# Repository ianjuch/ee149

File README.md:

ee149 smart light switch project
=====
Gabe Buckmaster
Ian Juch

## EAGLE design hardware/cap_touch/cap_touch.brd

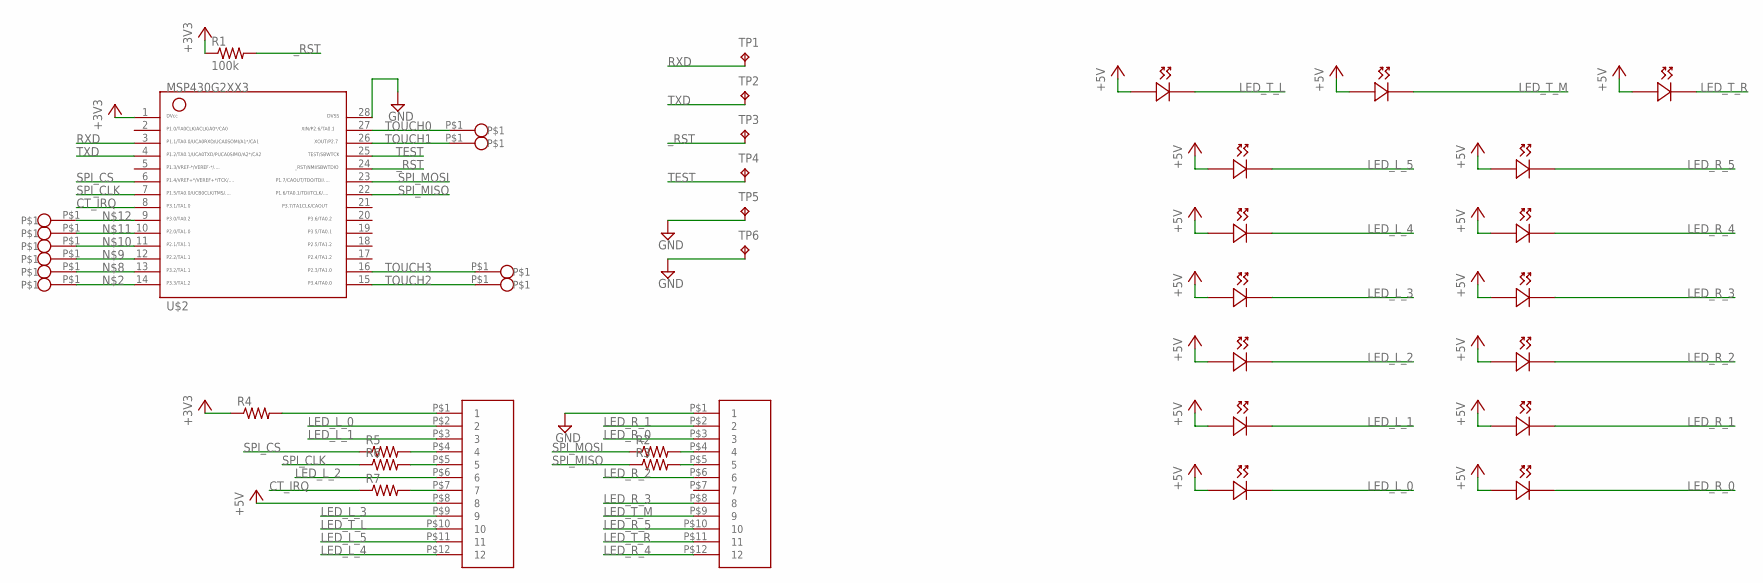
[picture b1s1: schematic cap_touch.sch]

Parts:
R1: 100k; 0603-RES
R2, R3, R4, R5, R6, R7: RESISTOR0805-RES; 0805
TP1, TP2, TP3, TP4, TP5, TP6: TPTP18SQ; TP18SQ
U$1, U$3: 12_PIN_SMT_HEADER; SMT_12PIN_HEADER
U$2: G2XX3---PW28; PW28
U$8, U$9, U$10, U$11, U$12, U$13, U$14, U$15, U$16, U$17, U$18, U$19, U$20, U$21, U$22: 597-6601-607F
U$25, U$26, U$27, U$28, U$29, U$30, U$31, U$32, U$33, U$34: VIA

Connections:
+3V3: R1.1, R4.1, U$2.1
+5V: U$1.P$8 (8), U$8.+ (R.POS), U$9.+ (R.POS), U$10.+ (R.POS), U$11.+ (R.POS), U$12.+ (R.POS), U$13.+ (R.POS), U$14.+ (R.POS), U$15.+ (R.POS), U$16.+ (R.POS), U$17.+ (R.POS), U$18.+ (R.POS), U$19.+ (R.POS), U$20.+ (R.POS), U$21.+ (R.POS), U$22.+ (R.POS)
CT_IRQ: R7.1, U$2.8
GND: TP5.TP, TP6.TP, U$2.28, U$3.P$1 (1)
LED_L_0: U$1.P$2 (2), U$21.- (R.NEG)
LED_L_1: U$1.P$3 (3), U$19.- (R.NEG)
LED_L_2: U$1.P$6 (6), U$17.- (R.NEG)
LED_L_3: U$1.P$9 (9), U$15.- (R.NEG)
LED_L_4: U$1.P$12 (12), U$13.- (R.NEG)
LED_L_5: U$1.P$11 (11), U$11.- (R.NEG)
LED_R_0: U$3.P$3 (3), U$22.- (R.NEG)
LED_R_1: U$3.P$2 (2), U$20.- (R.NEG)
LED_R_2: U$3.P$6 (6), U$18.- (R.NEG)
LED_R_3: U$3.P$8 (8), U$16.- (R.NEG)
LED_R_4: U$3.P$12 (12), U$14.- (R.NEG)
LED_R_5: U$3.P$10 (10), U$12.- (R.NEG)
LED_T_L: U$1.P$10 (10), U$8.- (R.NEG)
LED_T_M: U$3.P$9 (9), U$9.- (R.NEG)
LED_T_R: U$3.P$11 (11), U$10.- (R.NEG)
unnamed: R4.2, U$1.P$1 (1)
unnamed: U$2.14, U$29.P$1
unnamed: R2.2, U$3.P$4 (4)
unnamed: R3.2, U$3.P$5 (5)
unnamed: R5.2, U$1.P$4 (4)
unnamed: R6.2, U$1.P$5 (5)
unnamed: R7.2, U$1.P$7 (7)
unnamed: U$2.13, U$30.P$1
unnamed: U$2.12, U$31.P$1
unnamed: U$2.11, U$32.P$1
unnamed: U$2.10, U$33.P$1
unnamed: U$2.9, U$34.P$1
RXD: TP1.TP, U$2.3
SPI_CLK: R6.1, U$2.7
SPI_CS: R5.1, U$2.6
SPI_MISO: R3.1, U$2.22
SPI_MOSI: R2.1, U$2.23
TEST: TP4.TP, U$2.25
TOUCH0: U$2.27, U$26.P$1
TOUCH1: U$2.26, U$25.P$1
TOUCH2: U$2.15, U$28.P$1
TOUCH3: U$2.16, U$27.P$1
TXD: TP2.TP, U$2.4
_RST: R1.2, TP3.TP, U$2.24

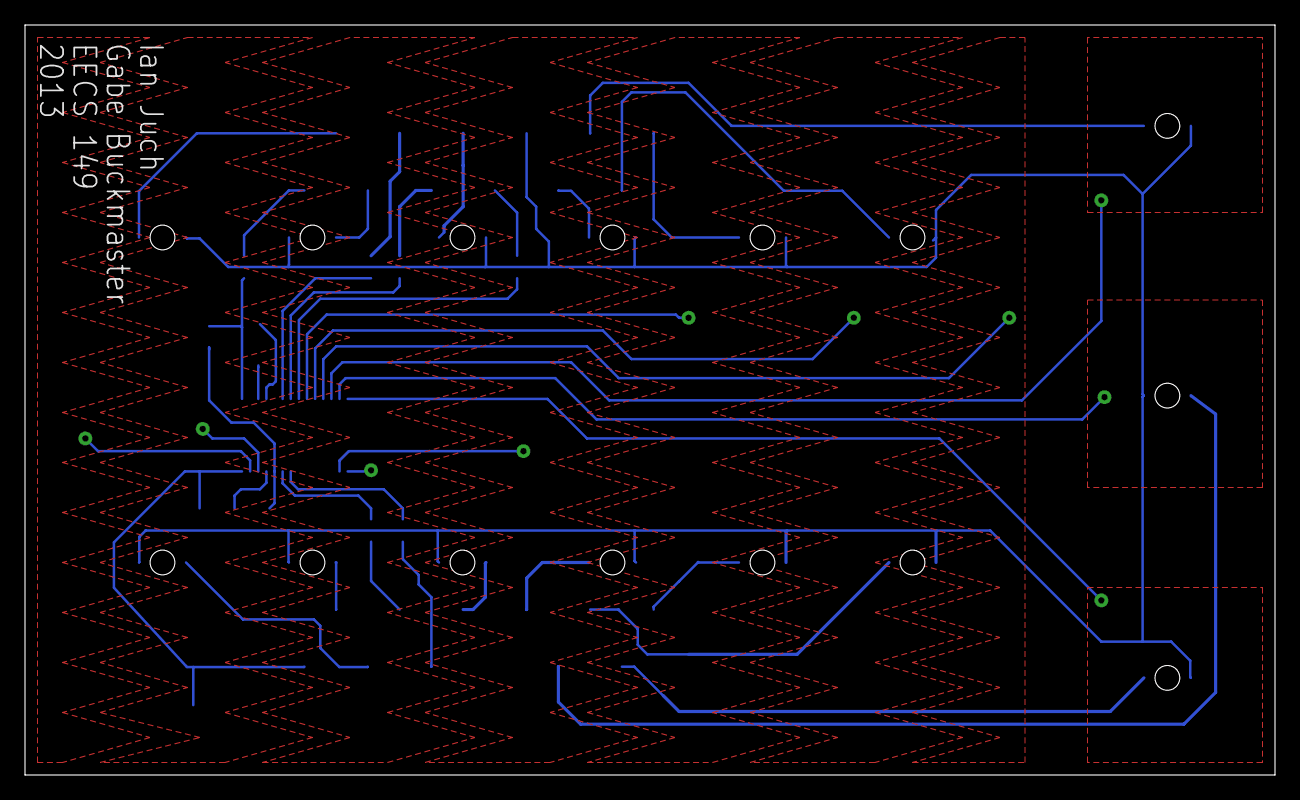
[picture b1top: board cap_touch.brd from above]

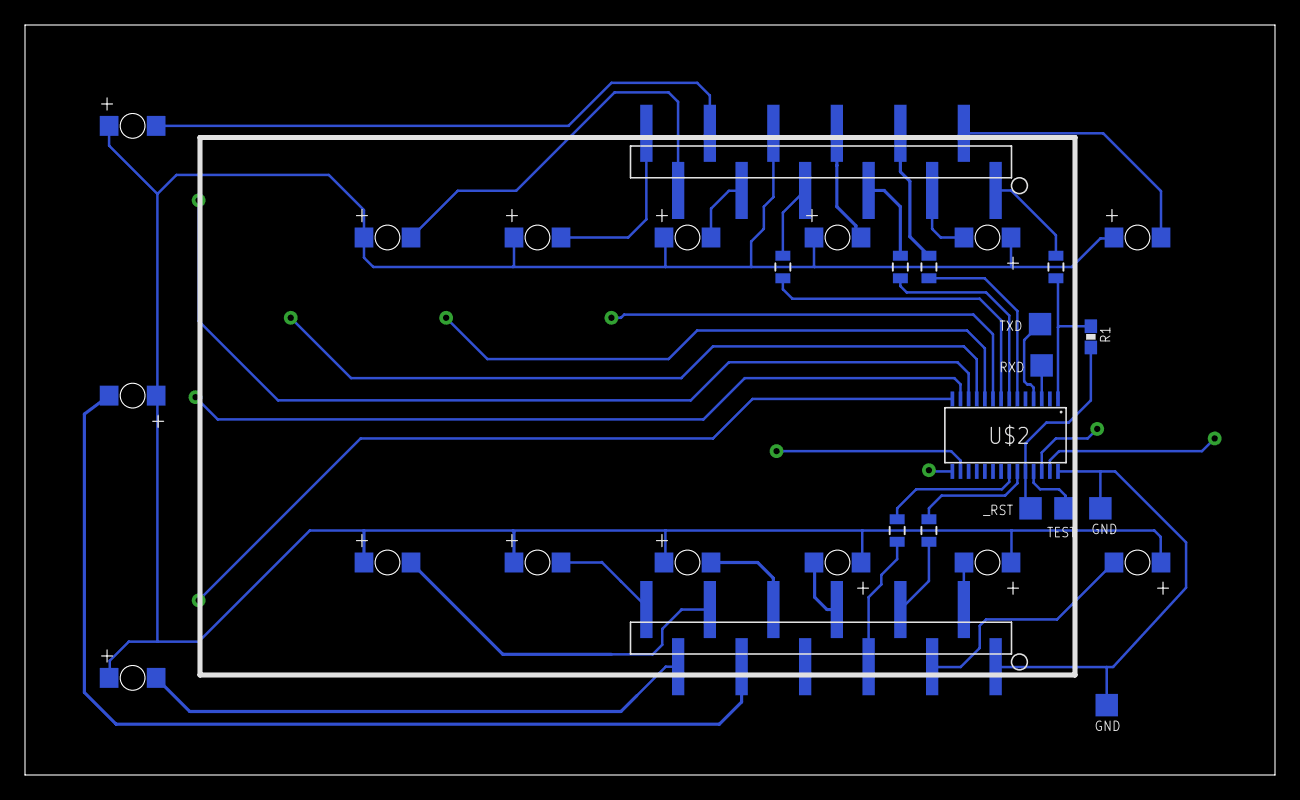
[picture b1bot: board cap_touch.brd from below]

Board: 2 copper layers, 100.0 x 60.0 mm, 41 parts (16 on the bottom side), 43 nets.

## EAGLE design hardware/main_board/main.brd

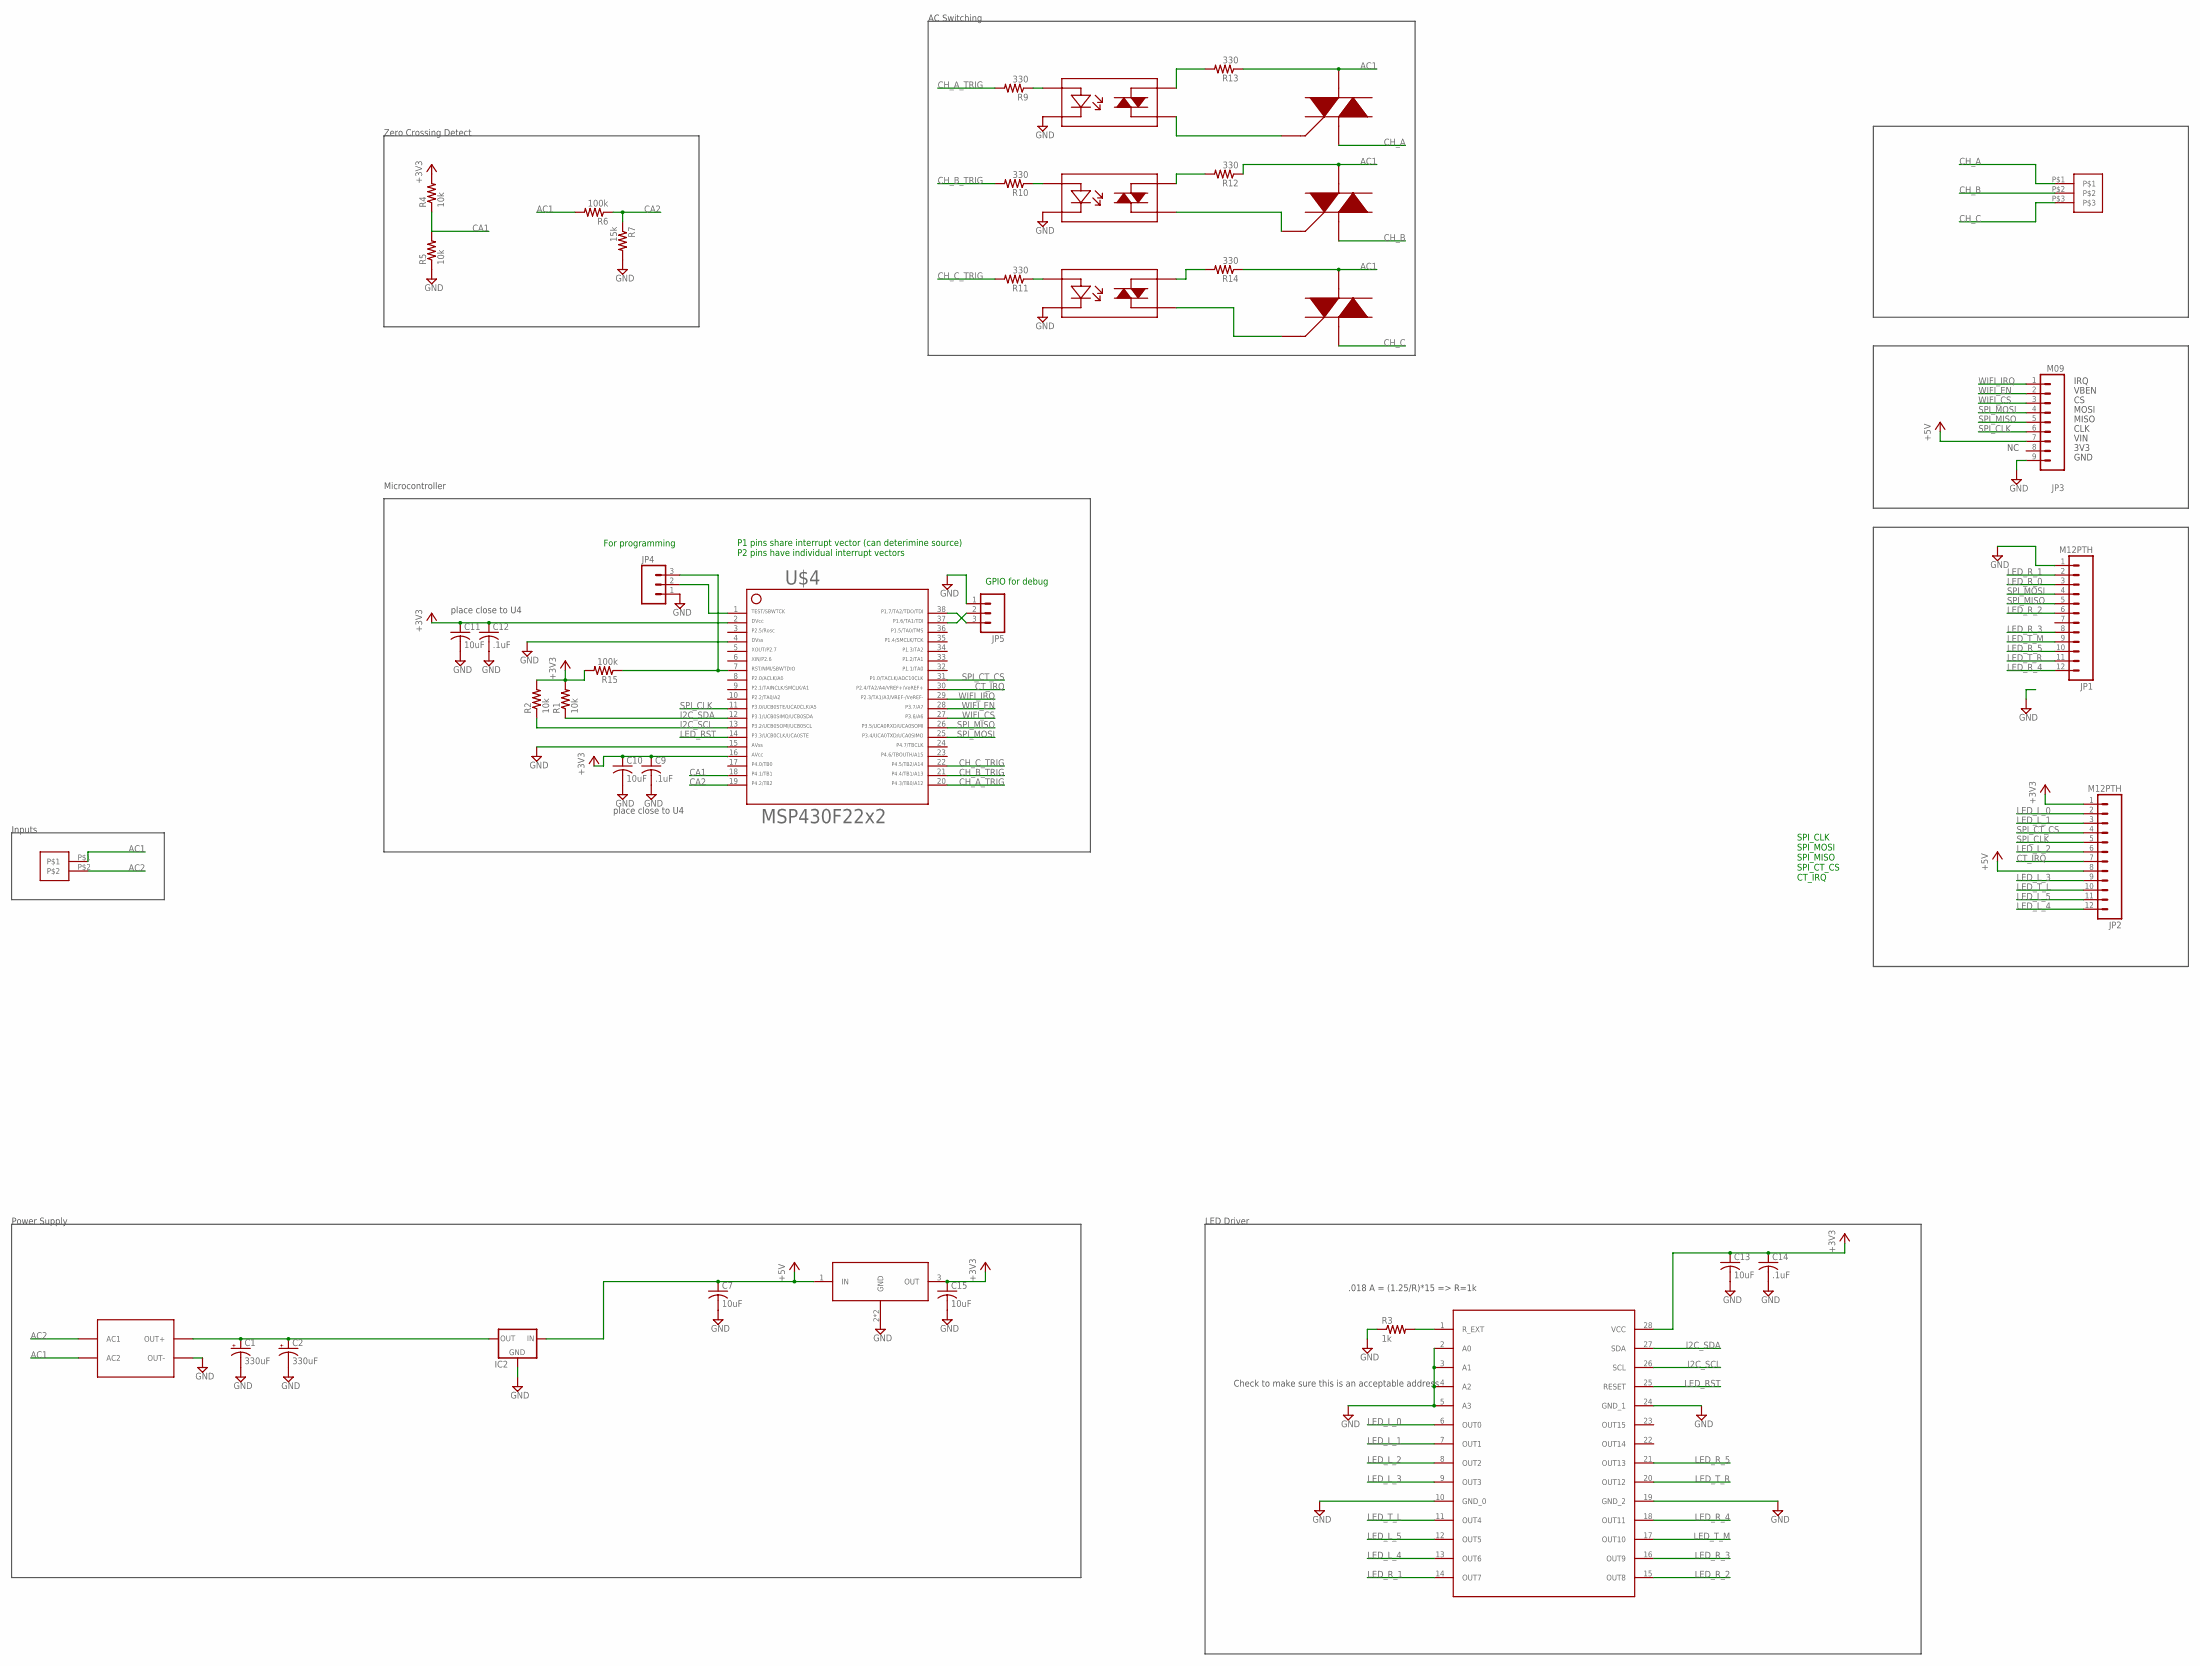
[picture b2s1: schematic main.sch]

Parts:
C1, C2: 330uF; RADIAL_CAN_SMD
C7, C10, C11, C13, C15: 10uF; C0603K
C9, C12, C14: .1uF; C0603K
IC2: V_REG_78XX-TO-220; TO-220-ALT
J1: 3-1437646-3
J2: 3-1437646-9
JP1, JP2: M12PTH; 1X12
JP3: M09; 1X09
JP4, JP5: M03PTH; 1X03
R1, R2, R4, R5: 10k; R0603
R3: 1k; R0603
R6, R15: 100k; R0603
R7: 15k; R0603
R9, R10, R11, R12, R13, R14: 330; R0603
U$1, U$6, U$7: FODM3011; SMD-4
U$2: DS1501S-T; DF-S
U$3: TLC59116; PW_28
U$4: F22X2---DA38; DA38
U$5: LM2937; SOT223
U$9, U$10, U$11: BT-137S-600D; SOT428

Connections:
+3V3: C9.1, C10.1, C11.1, C12.1, C13.1, C14.1, C15.1, JP2.1, R1.2, R2.2, R4.2, R15.2, U$3.28 (VCC), U$4.2, U$4.16, U$5.3 (OUT)
+5V: C7.1, IC2.IN, JP2.8, JP3.7, U$5.1 (IN)
AC1: J1.P$1, R6.2, R12.1, R13.1, R14.1, U$2.P$4 (AC2), U$9.T2 (S2), U$10.T2 (S2), U$11.T2 (S2)
AC2: J1.P$2, U$2.P$3 (AC1)
CA1: R4.1, R5.2, U$4.18
CA2: R6.1, R7.1, U$4.19
CH_A: J2.P$1, U$9.T1 (S1)
CH_A_TRIG: R9.2, U$4.20
CH_B: J2.P$2, U$10.T1 (S1)
CH_B_TRIG: R10.2, U$4.21
CH_C: J2.P$3, U$11.T1 (S1)
CH_C_TRIG: R11.2, U$4.22
CT_IRQ: JP2.7, U$4.30
GND: C1.-, C2.-, C7.2, C9.2, C10.2, C11.2, C12.2, C13.2, C14.2, C15.2, IC2.GND, JP1.1, JP3.9, JP4.1, JP5.1, R3.1, R5.1, R7.2, U$1.P$2 (LED-), U$2.P$2 (OUT-), U$3.2 (A0), U$3.3 (A1), U$3.4 (A2), U$3.5 (A3), U$3.10 (GND_0), U$3.19 (GND_2), U$3.24 (GND_1), U$4.4, U$4.15, U$5.2 (GND), U$5.4 (GND), U$6.P$2 (LED-), U$7.P$2 (LED-)
I2C_SCL: R2.1, U$3.26 (SCL), U$4.13
I2C_SDA: R1.1, U$3.27 (SDA), U$4.12
LED_L_0: JP2.2, U$3.6 (OUT0)
LED_L_1: JP2.3, U$3.7 (OUT1)
LED_L_2: JP2.6, U$3.8 (OUT2)
LED_L_3: JP2.9, U$3.9 (OUT3)
LED_L_4: JP2.12, U$3.13 (OUT6)
LED_L_5: JP2.11, U$3.12 (OUT5)
LED_RST: U$3.25 (RESET), U$4.14
LED_R_0: JP1.3
LED_R_1: JP1.2, U$3.14 (OUT7)
LED_R_2: JP1.6, U$3.15 (OUT8)
LED_R_3: JP1.8, U$3.16 (OUT9)
LED_R_4: JP1.12, U$3.18 (OUT11)
LED_R_5: JP1.10, U$3.21 (OUT13)
LED_T_L: JP2.10, U$3.11 (OUT4)
LED_T_M: JP1.9, U$3.17 (OUT10)
LED_T_R: JP1.11, U$3.20 (OUT12)
unnamed: C1.+, C2.+, IC2.OUT, U$2.P$1 (OUT+)
unnamed: JP4.3, R15.1, U$4.7
unnamed: JP4.2, U$4.1
unnamed: JP5.3, U$4.38
unnamed: JP5.2, U$4.37
unnamed: R3.2, U$3.1 (R_EXT)
unnamed: R9.1, U$1.P$1 (LED+)
unnamed: R10.1, U$6.P$1 (LED+)
unnamed: R11.1, U$7.P$1 (LED+)
unnamed: R14.2, U$7.P$3 (S1)
unnamed: U$7.P$4 (S2), U$11.G
unnamed: R12.2, U$6.P$3 (S1)
unnamed: U$6.P$4 (S2), U$10.G
unnamed: R13.2, U$1.P$3 (S1)
unnamed: U$1.P$4 (S2), U$9.G
SPI_CLK: JP2.5, JP3.6, U$4.11
SPI_CT_CS: JP2.4, U$4.31
SPI_MISO: JP1.5, JP3.5, U$4.26
SPI_MOSI: JP1.4, JP3.4, U$4.25
WIFI_CS: JP3.3, U$4.27
WIFI_EN: JP3.2, U$4.28
WIFI_IRQ: JP3.1, U$4.29

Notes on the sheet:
Inputs
Power Supply
Microcontroller
place close to U4
Check to make sure this is an acceptable address
GND
3V3
VIN
CLK
MISO
MOSI
VBEN
IRQ
.018 A = (1.25/R)*15 => R=1k
LED Driver
Zero Crossing Detect
AC Switching
SPI_CLK SPI_MOSI SPI_MISO SPI_CT_CS CT_IRQ
P1 pins share interrupt vector (can deterimine source) P2 pins have individual interrupt vectors
For programming
GPIO for debug

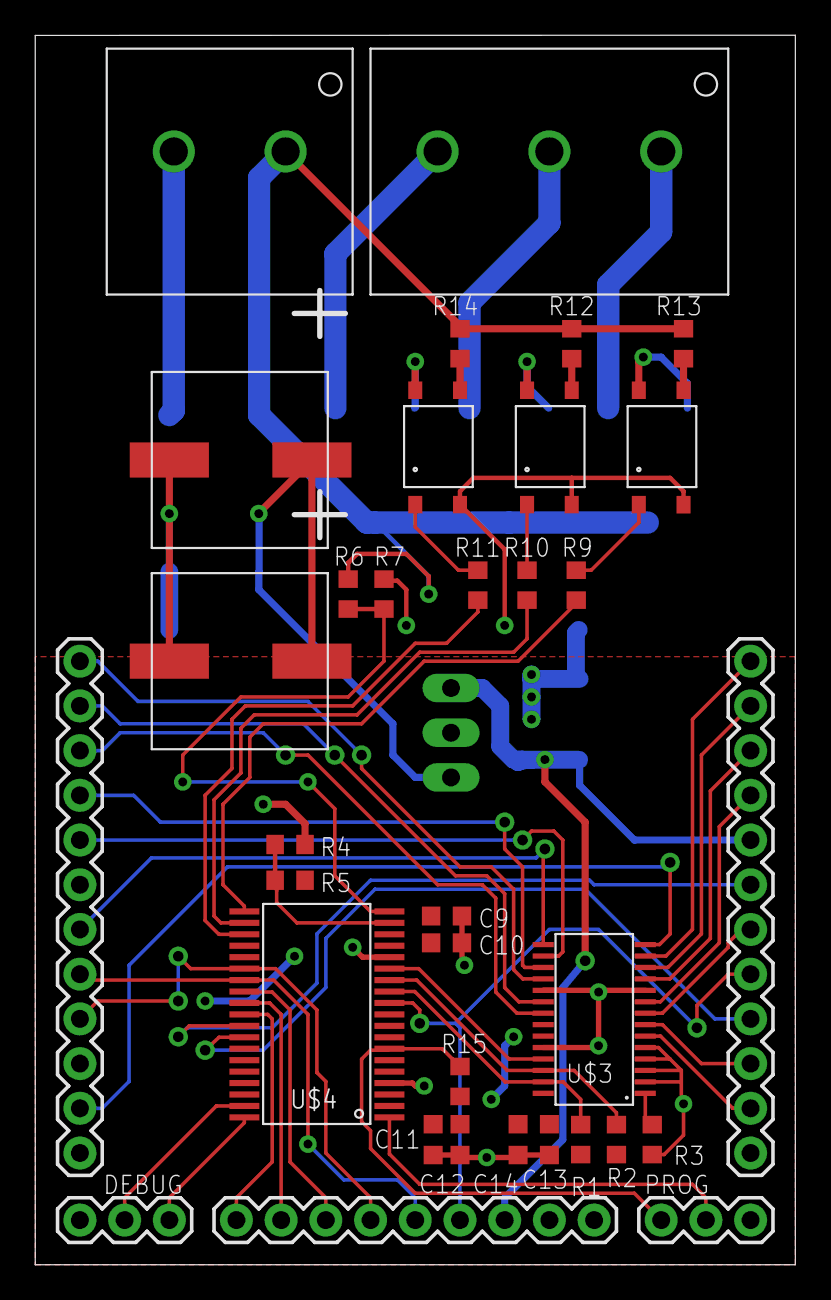
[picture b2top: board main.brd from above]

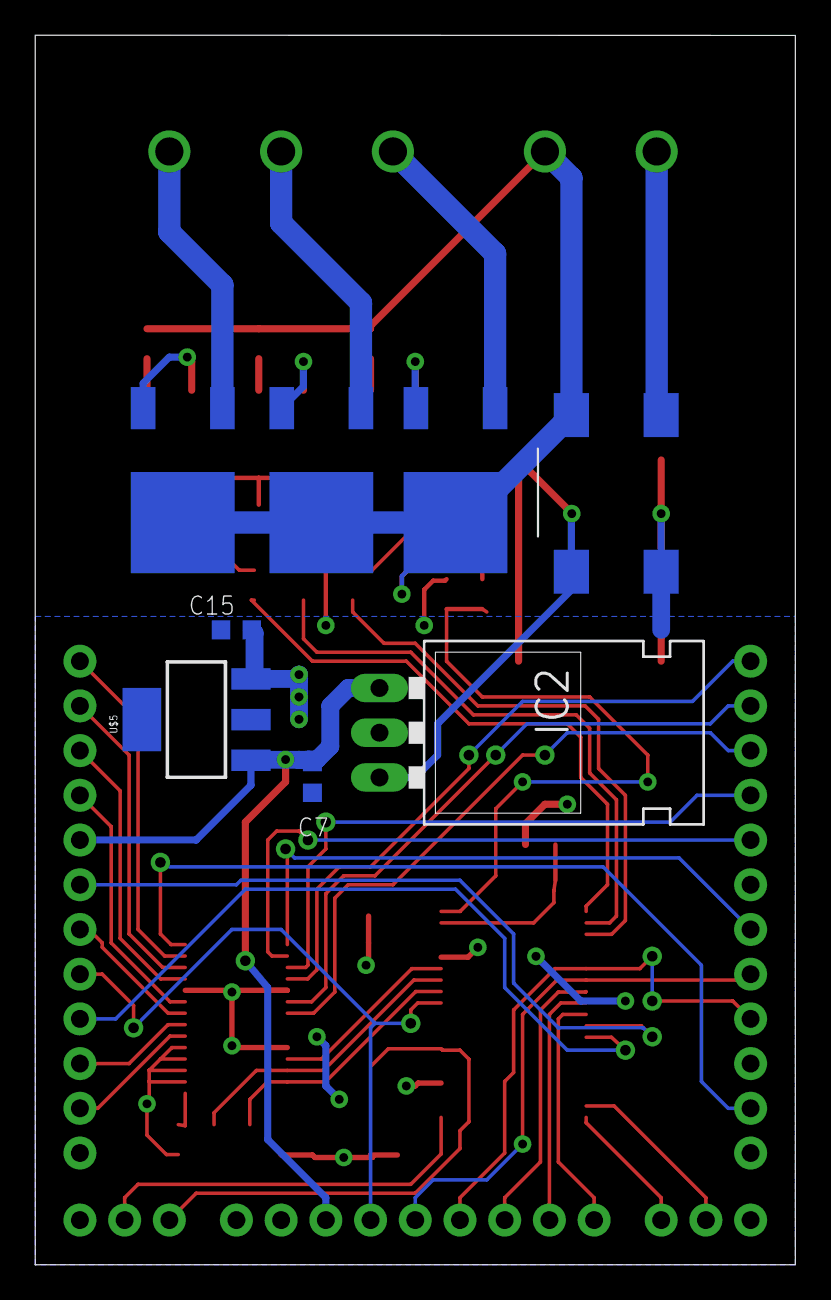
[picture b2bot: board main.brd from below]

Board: 2 copper layers, 43.2 x 69.8 mm, 42 parts (8 on the bottom side), 53 nets.

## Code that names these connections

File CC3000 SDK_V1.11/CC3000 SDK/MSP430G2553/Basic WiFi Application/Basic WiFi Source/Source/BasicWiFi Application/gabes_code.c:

#include <msp430.h>
//#include <legacymsp430.h>
//#include <stdint.h>


#define LED_T_L 0x6
#define LED_T_M 0xc
#define LED_T_R 0xe
#define LED_L_0 0x2
#define LED_L_1 0x3
#define LED_L_2 0x4
#define LED_L_3 0x5
#define LED_L_4 0x8
#define LED_L_5 0x7
#define LED_R_0 :(
#define LED_R_1 0x9
#define LED_R_2 0xa
#define LED_R_3 0xb
#define LED_R_4 0xd
#define LED_R_5 0xf

void init();
void delay_ms();
void i2cWriteByte(unsigned char, unsigned char, unsigned char);
unsigned char spiReadByte();
void spiInit();

void fadeOn(unsigned char ledAddr)
{
    unsigned char i = 0;
    while (i < 255)
    {
        i += 5;
        i2cWriteByte(ledAddr, i, 0x60);
        delay_ms(2);
    }
}
void fadeOff(unsigned char ledAddr)
{
    unsigned char i = 255;
    while (i > 0)
    {
        i -= 5;
        i2cWriteByte(ledAddr, i, 0x60);
        delay_ms(2);
    }
}

int main(void)
{
    init();
    //delay_ms(500);

    //debug pins
    P1DIR = BIT6|BIT7;
    P1SEL &= ~BIT6;
    P1SEL &= ~BIT7;
    P1SEL2 &= ~BIT6;
    P1SEL2 &= ~BIT7;
    
    
    i2cWriteByte(0x00, 0x00, 0x60);
    delay_ms(5);
    i2cWriteByte(0x00, 0x00, 0x60);
    delay_ms(5);
    i2cWriteByte(0x14, 0xaa, 0x60);
    delay_ms(5);
    i2cWriteByte(0x15, 0xaa, 0x60);
    delay_ms(5);
    i2cWriteByte(0x16, 0xaa, 0x60);
    delay_ms(5);
    i2cWriteByte(0x17, 0xaa, 0x60);
    
    
    unsigned char lastTouchLocation = 0xFF;
    while (1)
    {
        fadeOn(LED_L_5);
        fadeOff(LED_L_5);
        unsigned char receivedByte = spiReadByte();
        if (receivedByte & 0x80)
        {
            switch (receivedByte&0x7F)
            {
                case 1:
                    fadeOn(LED_T_L);
                    break;
                case 2:
                    fadeOn(LED_T_M);
                    break;
                case 3:
                    fadeOn(LED_T_R);
                    break;
                    
                default:
                    break;
            }
        }
        else
        {
            // scroll value
            //fadeOff(LED_T_L);
            //fadeOff(LED_T_M);
            //fadeOff(LED_T_R);
            //fadeOn(LED_T_M);
        }
        /*
        if (lastTouchLocation != touchLocation)
        {
            switch (touchLocation)
            {
                case 0:
                    fadeOn(LED_L_1);
                    break;
                case 1:
                    fadeOn(LED_L_2);
                    break;
                case 2:
                    fadeOn(LED_L_3);
                    break;
                case 3:
                    fadeOn(LED_L_4);
                    break;
                case 4:
                    fadeOn(LED_L_5);
                    break;
                    
                default:
                    break;
            }
            lastTouchLocation = touchLocation;
        
        }
        else
        {
            delay_ms(100);
        }
        */
        
        //spiReadByte();
        
        /*
        if (spiReadByte() & 0x01)
        {
            fadeOn(LED_T_R);
            fadeOff(LED_T_R);
        }
        else
        {
            fadeOn(LED_T_L);
            fadeOff(LED_T_L);
        }
         */
        
    }

    
    return 0;
}

void init(void)
{
    WDTCTL = WDTPW+WDTHOLD;
    
    // Set clock to 1 MHz
    DCOCTL = 0;
    BCSCTL1 = CALBC1_1MHZ;
    DCOCTL = CALDCO_1MHZ;
    
    //SMCLK = 1 MHz / 8 = 125 KHz (SLAU144E p.5-15)
    //BCSCTL2 |= DIVS_3;
    
    P3SEL |= BIT1|BIT2; //set to I2C mode
    
    P3DIR |= BIT3;
    P3OUT |= BIT3;
    
    
    // Set up I2C
    UCB0BR0 = 10; // Divide clock source by 10
    UCB0CTL0 = UCSYNC|UCMST|UCMODE1|UCMODE0;
    UCB0CTL1 = UCSSEL1|UCSSEL0; // Clears reset
    
    spiInit();
}

void spiInit()
{
    // Connect clock pin
    P3SEL |= BIT0;
    P3SEL2 &= ~BIT0;
    
    // Connect MISO
    P3SEL |= BIT5;
    P3SEL2 &= ~BIT5;
    
    // Connect MOSI
    P3SEL |= BIT4;
    P3SEL2 &= ~BIT4;
    
    UCA0CTL1 |= UCSWRST;
    UCA0CTL0 |= UCMST|UCSYNC;
    UCA0CTL1 |= UCSSEL0|UCSSEL1|UCSWRST;
    UCA0BR0 = 1;
    UCA0CTL1 &= ~UCSWRST;
}

unsigned char spiReadByte()
{
    // Apparently the UCSI resets itself after receiving a byte...
    UCA0CTL1 &= ~UCSWRST;
    
    
    unsigned char rv;
    UCA0TXBUF = 0x55;
    while (!(IFG2 & UCA0RXIFG))
    {
        //__asm__("nop");
    }
    rv = UCA0RXBUF;
    return rv;
}

void i2cWriteByte(unsigned char data0, unsigned char data1, unsigned char address)
{
    UCB0I2CSA = address;
    UCB0CTL1 |= UCTR;
    UCB0CTL1 |= UCTXSTT;
    while (!(IFG2 & UCB0TXIFG))
    {
        //__asm__("nop");
    }
    UCB0TXBUF = data0;
    while (!(IFG2 & UCB0TXIFG))
    {
        //__asm__("nop");
    }
    UCB0TXBUF = data1;
    while (!(IFG2 & UCB0TXIFG))
    {
        //__asm__("nop");
    }
    UCB0CTL1 |= UCTXSTP;
    
    // set UCTXSTP or write another character to the buffer
}


void delay_ms(int d)
{
    int i;
    for (i = 0; i < d; i++)
        __delay_cycles(1000);
}

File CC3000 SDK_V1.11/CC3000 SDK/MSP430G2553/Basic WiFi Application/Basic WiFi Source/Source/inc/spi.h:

/*****************************************************************************
*
*  spi.h  - CC3000 Host Driver Implementation.
*  Copyright (C) 2011 Texas Instruments Incorporated - http://www.ti.com/
*
*  Redistribution and use in source and binary forms, with or without
*  modification, are permitted provided that the following conditions
*  are met:
*
*    Redistributions of source code must retain the above copyright
*    notice, this list of conditions and the following disclaimer.
*
*    Redistributions in binary form must reproduce the above copyright
*    notice, this list of conditions and the following disclaimer in the
*    documentation and/or other materials provided with the   
*    distribution.
*
*    Neither the name of Texas Instruments Incorporated nor the names of
*    its contributors may be used to endorse or promote products derived
*    from this software without specific prior written permission.
*
*  THIS SOFTWARE IS PROVIDED BY THE COPYRIGHT HOLDERS AND CONTRIBUTORS 
*  "AS IS" AND ANY EXPRESS OR IMPLIED WARRANTIES, INCLUDING, BUT NOT 
*  LIMITED TO, THE IMPLIED WARRANTIES OF MERCHANTABILITY AND FITNESS FOR
*  A PARTICULAR PURPOSE ARE DISCLAIMED. IN NO EVENT SHALL THE COPYRIGHT 
*  OWNER OR CONTRIBUTORS BE LIABLE FOR ANY DIRECT, INDIRECT, INCIDENTAL, 
*  SPECIAL, EXEMPLARY, OR CONSEQUENTIAL DAMAGES (INCLUDING, BUT NOT 
*  LIMITED TO, PROCUREMENT OF SUBSTITUTE GOODS OR SERVICES; LOSS OF USE,
*  DATA, OR PROFITS; OR BUSINESS INTERRUPTION) HOWEVER CAUSED AND ON ANY
*  THEORY OF LIABILITY, WHETHER IN CONTRACT, STRICT LIABILITY, OR TORT 
*  (INCLUDING NEGLIGENCE OR OTHERWISE) ARISING IN ANY WAY OUT OF THE USE 
*  OF THIS SOFTWARE, EVEN IF ADVISED OF THE POSSIBILITY OF SUCH DAMAGE.
*
*****************************************************************************/


#ifndef __SPI_H__
#define __SPI_H__

#include <string.h>
#include <stdlib.h>
#include <stdio.h>



//*****************************************************************************
//
// If building with a C++ compiler, make all of the definitions in this header
// have a C binding.
//
//*****************************************************************************
#ifdef  __cplusplus
extern "C" {
#endif

typedef void (*gcSpiHandleRx)(void *p);
typedef void (*gcSpiHandleTx)(void);

extern unsigned char wlan_tx_buffer[];


#define MOSI_MISO_PORT_SEL    P3SEL
#define MOSI_MISO_PORT_SEL2   P3SEL2
#define SPI_MISO_PIN         BIT5//BIT6
#define SPI_MOSI_PIN         BIT4//BIT7

#define SPI_CLK_PORT_SEL    P3SEL
#define SPI_CLK_PORT_SEL2   P3SEL2
#define SPI_CLK_PIN         BIT0//BIT5

#define SPI_IRQ_PORT    P2IE
#define SPI_IFG_PORT    P2IFG
#define SPI_IRQ_PIN     BIT3//BIT6
//*****************************************************************************
//
// Prototypes for the APIs.
//
//*****************************************************************************
extern void SpiOpen(gcSpiHandleRx pfRxHandler);
extern void SpiClose(void);
extern long SpiWrite(unsigned char *pUserBuffer, unsigned short usLength);
extern void SpiResumeSpi(void);
extern void SpiConfigureHwMapping(	unsigned long ulPioPortAddress,
									unsigned long ulPort, 
									unsigned long ulSpiCs, 
									unsigned long ulPortInt, 
									unsigned long uluDmaPort,
									unsigned long ulSsiPortAddress,
									unsigned long ulSsiTx,
									unsigned long ulSsiRx,
									unsigned long ulSsiClck);
extern void SpiCleanGPIOISR(void);
extern int init_spi(void);
extern long TXBufferIsEmpty(void);
extern long RXBufferIsEmpty(void);
//*****************************************************************************
//
// Mark the end of the C bindings section for C++ compilers.
//
//*****************************************************************************
#ifdef  __cplusplus
}
#endif // __cplusplus

#endif

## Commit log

2013-10-27 README update
2013-11-22 adding basic wifi example code from TI
2013-12-14 makefile that actually works
2013-12-15 UI pretty much works!
    Capacitive touch works, LEDs work, although the buttons on top block as
    they’re fading between each other.
2013-12-15 TRIACS turn on and off
2013-12-15 adding source files with changes
2013-12-16 Syncs timer with mains frequency
2013-12-16 1 channel of TRIAC output working
2013-12-17 CT, 3 channel output control, LEDs work
2013-12-17 Channel state memory works
2013-12-17 change P3SEL control pins for SPI
2013-12-21 Added hardware design files

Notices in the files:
parts and their libraries:
SparkFun-Passives: Licensing: CC v3.0 Share-Alike You are welcome to use this library for commercial purposes.
